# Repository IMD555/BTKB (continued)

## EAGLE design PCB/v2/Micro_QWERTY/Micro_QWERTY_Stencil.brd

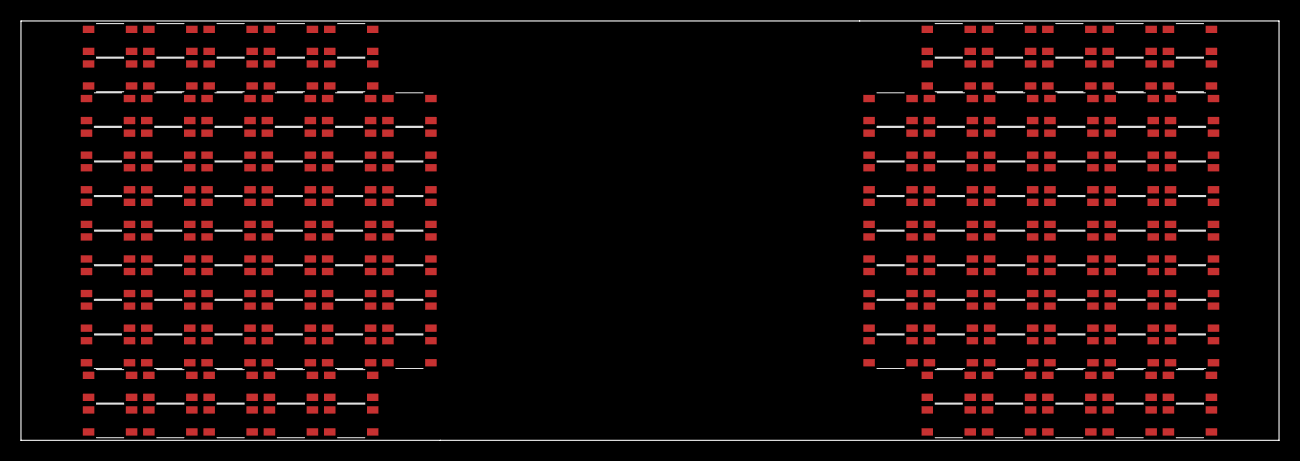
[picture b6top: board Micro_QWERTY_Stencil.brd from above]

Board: 2 copper layers, 120.0 x 40.0 mm, 136 parts (0 on the bottom side), 40 nets, no tracks yet.

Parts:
SW1, SW112: SKRP(ALPS); TVAU10-025
SW2, SW3, SW4, SW5, SW6, SW7, SW8, SW9, SW10, SW11, SW12, SW13, SW14, SW15, SW16, SW17, SW18, SW19, SW20, SW21, SW22, SW23, SW24, SW25, SW26, SW27, SW28, SW29, SW30, SW31, SW32, SW33, SW34, SW35, SW36, SW37, SW38, SW39, SW40, SW41, SW42, SW43, SW44, SW45, SW46, SW47, SW48, SW49, SW50, SW51, SW52, SW53, SW54, SW55, SW56, SW57, SW58, SW59, SW60, SW61, SW62, SW63, SW64, SW65, SW66, SW67, SW68, SW101, SW102, SW103, SW104, SW105, SW106, SW107, SW108, SW109, SW110, SW111, SW113, SW114, SW115, SW116, SW117, SW118, SW119, SW120, SW121, SW122, SW123, SW124, SW125, SW126, SW127, SW128, SW129, SW130, SW131, SW132, SW133, SW134, SW135, SW136, SW137, SW138, SW139, SW140, SW141, SW142, SW143, SW144, SW145, SW146, SW147, SW148, SW149, SW150, SW151, SW152, SW153, SW154, SW155, SW156, SW157, SW158, SW159, SW160, SW163, SW164, SW165, SW166, SW167, SW168, SW169, SW170: SW_4PTVAU10-025; TVAU10-025

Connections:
C0: SW112.P$2, SW124.P$1
C1: SW111.P$2, SW123.P$1
C2: SW122.P$2, SW134.P$1
C3: SW121.P$2, SW133.P$1
C4: SW120.P$2, SW132.P$1
C5: SW119.P$2, SW131.P$1
C6: SW118.P$4, SW130.P$3
C7: SW117.P$4, SW129.P$3
C8: SW116.P$4, SW128.P$3
C9: SW115.P$4, SW127.P$3
C10: SW102.P$4, SW114.P$3
C11: SW101.P$4, SW113.P$3
C12: SW1.P$2, SW2.P$1
C13: SW6.P$2, SW7.P$1
C14: SW12.P$2, SW13.P$1
C15: SW18.P$2, SW19.P$1
C16: SW24.P$2, SW25.P$1
C17: SW30.P$2, SW31.P$1
C18: SW36.P$4, SW37.P$3
C19: SW42.P$4, SW43.P$3
C20: SW48.P$4, SW49.P$3
C21: SW54.P$4, SW55.P$3
C22: SW59.P$4, SW60.P$3
C23: SW64.P$4, SW65.P$3
unnamed: SW123.P$2, SW135.P$1
unnamed: SW114.P$4, SW126.P$3
unnamed: SW7.P$2, SW8.P$1
unnamed: SW60.P$4, SW61.P$3
R0: SW101.P$1, SW102.P$1, SW103.P$1, SW104.P$1, SW105.P$1, SW106.P$1, SW107.P$3, SW108.P$3, SW109.P$3, SW110.P$3, SW111.P$3, SW112.P$3
R1: SW113.P$1, SW114.P$1, SW115.P$1, SW116.P$1, SW117.P$1, SW118.P$1, SW119.P$3, SW120.P$3, SW121.P$3, SW122.P$3, SW123.P$3, SW124.P$3
R2: SW125.P$1, SW126.P$1, SW127.P$1, SW128.P$1, SW129.P$1, SW130.P$1, SW131.P$3, SW132.P$3, SW133.P$3, SW134.P$3, SW135.P$3, SW136.P$3
R3: SW137.P$1, SW138.P$1, SW139.P$1, SW140.P$1, SW141.P$1, SW142.P$1, SW143.P$3, SW144.P$3, SW145.P$3, SW146.P$3, SW147.P$3, SW148.P$3
R4: SW149.P$1, SW150.P$1, SW151.P$1, SW152.P$1, SW153.P$1, SW154.P$1, SW155.P$3, SW156.P$3, SW157.P$3, SW158.P$3, SW159.P$3, SW160.P$3
R5: SW163.P$1, SW164.P$1, SW165.P$1, SW166.P$1, SW167.P$3, SW168.P$3, SW169.P$3, SW170.P$3
R6: SW1.P$3, SW6.P$3, SW11.P$3, SW17.P$3, SW23.P$3, SW29.P$3, SW35.P$1, SW41.P$1, SW47.P$1, SW53.P$1, SW59.P$1, SW64.P$1
R7: SW2.P$3, SW7.P$3, SW12.P$3, SW18.P$3, SW24.P$3, SW30.P$3, SW36.P$1, SW42.P$1, SW48.P$1, SW54.P$1, SW60.P$1, SW65.P$1
R8: SW3.P$3, SW8.P$3, SW13.P$3, SW19.P$3, SW25.P$3, SW31.P$3, SW37.P$1, SW43.P$1, SW49.P$1, SW55.P$1, SW61.P$1, SW66.P$1
R9: SW4.P$3, SW9.P$3, SW14.P$3, SW20.P$3, SW26.P$3, SW32.P$3, SW38.P$1, SW44.P$1, SW50.P$1, SW56.P$1, SW62.P$1, SW67.P$1
R10: SW5.P$3, SW10.P$3, SW15.P$3, SW21.P$3, SW27.P$3, SW33.P$3, SW39.P$1, SW45.P$1, SW51.P$1, SW57.P$1, SW63.P$1, SW68.P$1
R11: SW16.P$3, SW22.P$3, SW28.P$3, SW34.P$3, SW40.P$1, SW46.P$1, SW52.P$1, SW58.P$1

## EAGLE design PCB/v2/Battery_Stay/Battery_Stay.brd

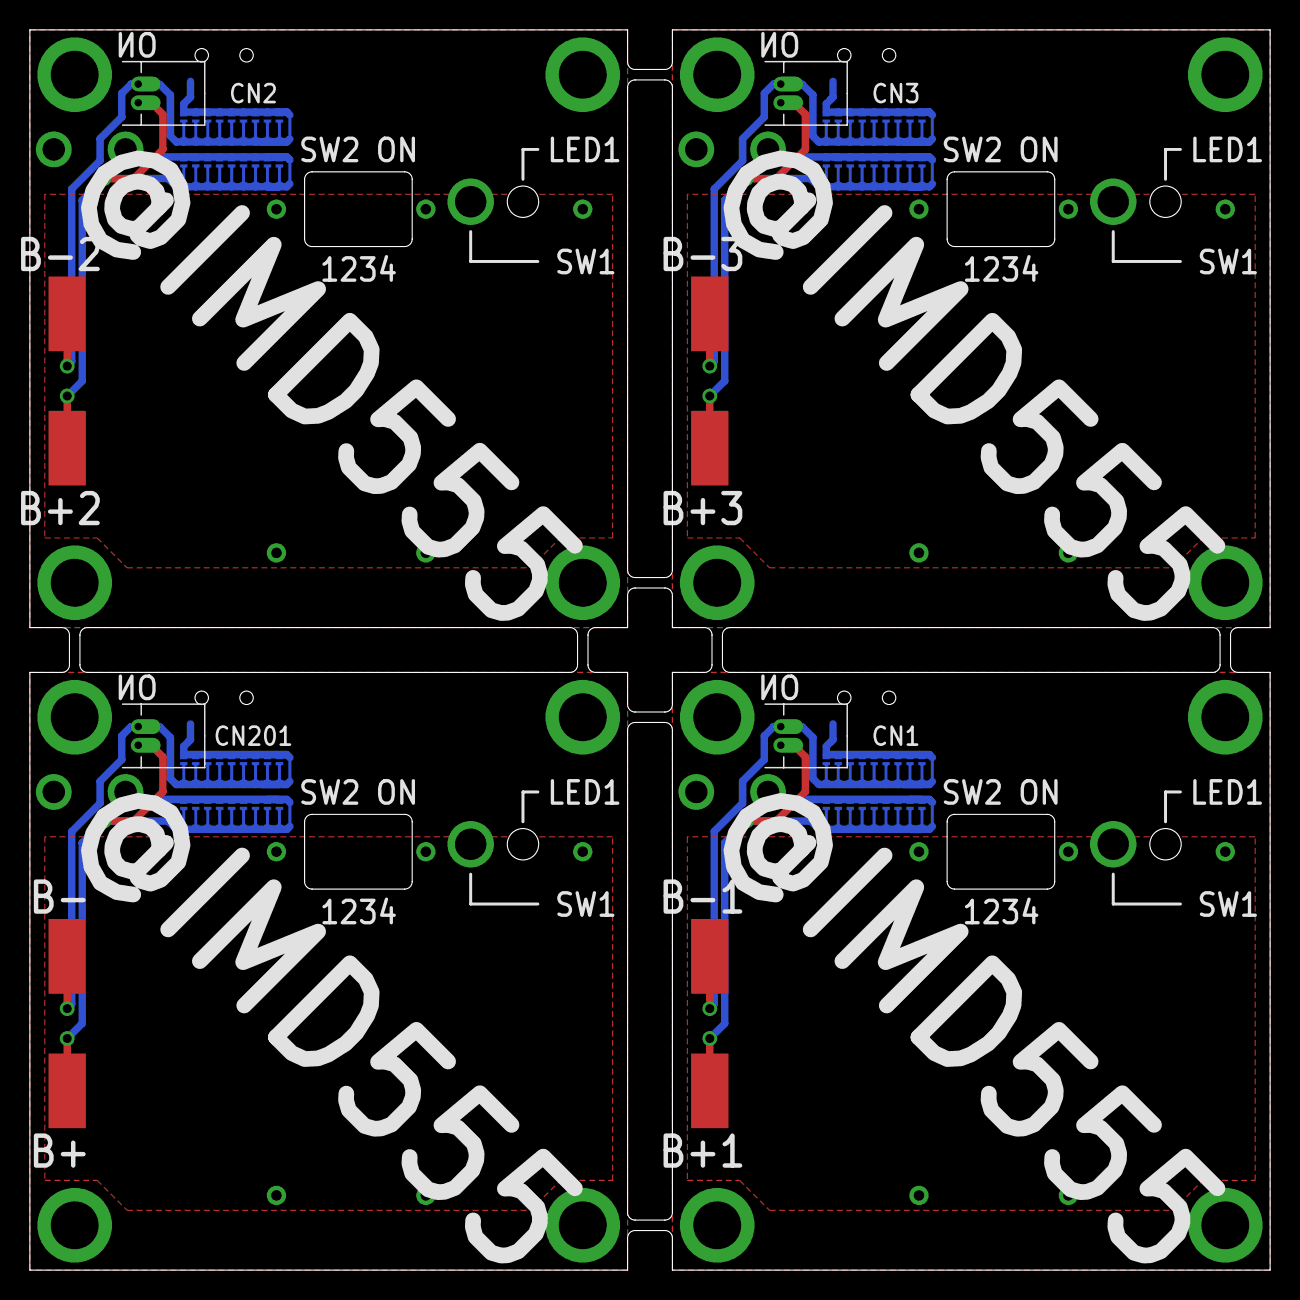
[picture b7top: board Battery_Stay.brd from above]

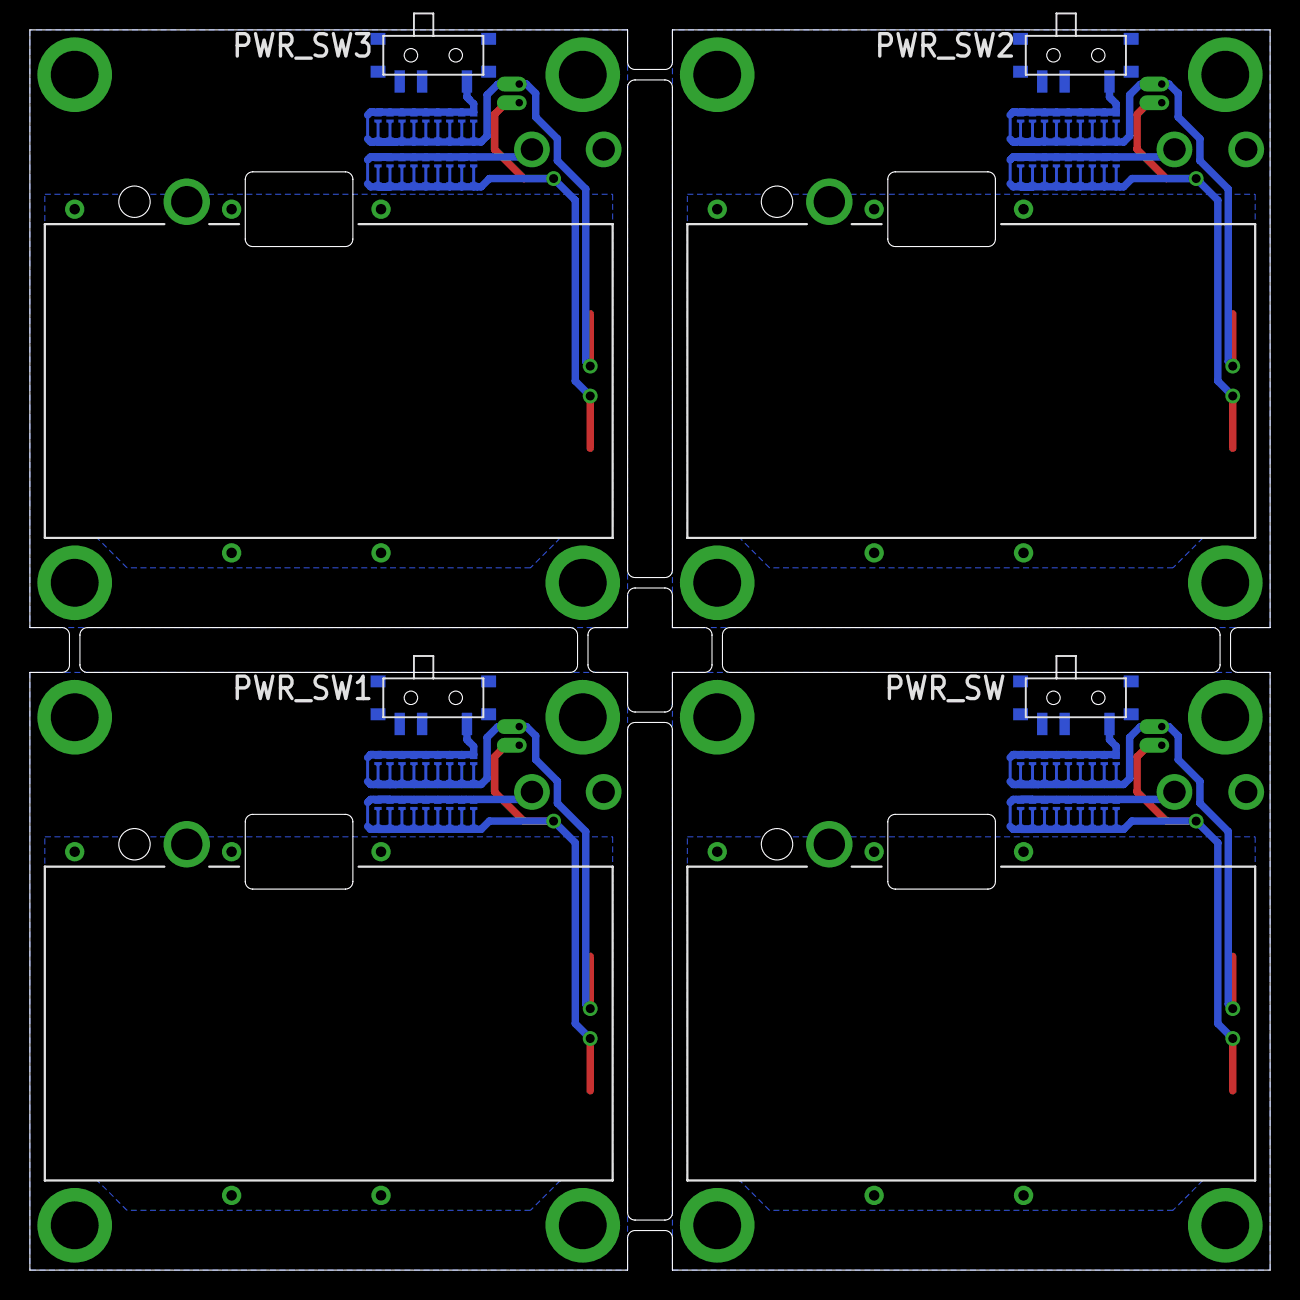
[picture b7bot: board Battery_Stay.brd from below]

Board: 2 copper layers, 83.0 x 83.0 mm, 88 parts (76 on the bottom side), 20 nets.

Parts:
B+, B+1, B+2, B+3: +; SMD2,5-5
B-, B-1, B-2, B-3: -; SMD2,5-5
CN1, CN2, CN3, CN201: 53048-0210
F1, F2, F3, F4, F5, F6, F7, F8, F9, F10, F11, F12, F13, F14, F15, F16, F17, F18, F19, F20, F21, F22, F23, F24, F25, F26, F27, F28, F29, F30, F31, F32, F33, F34, F35, F36, F37, F38, F39, F40, F41, F42, F43, F44, F45, F46, F47, F48, F49, F50, F51, F52, F53, F54, F55, F56, F57, F58, F59, F60, F61, F62, F63, F64, F65, F66, F67, F68, F69, F70, F71, F72: FUSEPAT0.2; FUSE_PAT1
PWR_SW, PWR_SW1, PWR_SW2, PWR_SW3: MA12R

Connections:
GND: PWR_SW.P$2, PWR_SW.P$3, PWR_SW.P$4, PWR_SW.P$5, PWR_SW.P$6, PWR_SW.P$7
GND1: PWR_SW1.P$2, PWR_SW1.P$3, PWR_SW1.P$4, PWR_SW1.P$5, PWR_SW1.P$6, PWR_SW1.P$7
GND2: PWR_SW2.P$2, PWR_SW2.P$3, PWR_SW2.P$4, PWR_SW2.P$5, PWR_SW2.P$6, PWR_SW2.P$7
GND3: PWR_SW3.P$2, PWR_SW3.P$3, PWR_SW3.P$4, PWR_SW3.P$5, PWR_SW3.P$6, PWR_SW3.P$7
unnamed: F1.P$1, F2.P$1, F3.P$1, F4.P$1, F5.P$1, F6.P$1, F13.P$1, F14.P$1, F15.P$1, PWR_SW.P$1
unnamed: B-.1, CN201.2, F1.P$2, F2.P$2, F3.P$2, F4.P$2, F5.P$2, F6.P$2, F13.P$2, F14.P$2, F15.P$2
unnamed: F7.P$1, F8.P$1, F9.P$1, F10.P$1, F11.P$1, F12.P$1, F17.P$1, F18.P$1, F19.P$1
unnamed: B+.1, CN201.1, F7.P$2, F8.P$2, F9.P$2, F10.P$2, F11.P$2, F12.P$2, F17.P$2, F18.P$2, F19.P$2
unnamed: F16.P$1, F23.P$1, F24.P$1, F25.P$1, F26.P$1, F27.P$1, F31.P$1, F32.P$1, F33.P$1, PWR_SW1.P$1
unnamed: B-1.1, CN1.2, F16.P$2, F23.P$2, F24.P$2, F25.P$2, F26.P$2, F27.P$2, F31.P$2, F32.P$2, F33.P$2
unnamed: F20.P$1, F21.P$1, F22.P$1, F28.P$1, F29.P$1, F30.P$1, F34.P$1, F35.P$1, F36.P$1
unnamed: B+1.1, CN1.1, F20.P$2, F21.P$2, F22.P$2, F28.P$2, F29.P$2, F30.P$2, F34.P$2, F35.P$2, F36.P$2
unnamed: F37.P$1, F41.P$1, F42.P$1, F43.P$1, F44.P$1, F45.P$1, F49.P$1, F50.P$1, F51.P$1, PWR_SW2.P$1
unnamed: B-2.1, CN2.2, F37.P$2, F41.P$2, F42.P$2, F43.P$2, F44.P$2, F45.P$2, F49.P$2, F50.P$2, F51.P$2
unnamed: F38.P$1, F39.P$1, F40.P$1, F46.P$1, F47.P$1, F48.P$1, F52.P$1, F53.P$1, F54.P$1
unnamed: B+2.1, CN2.1, F38.P$2, F39.P$2, F40.P$2, F46.P$2, F47.P$2, F48.P$2, F52.P$2, F53.P$2, F54.P$2
unnamed: F55.P$1, F59.P$1, F60.P$1, F61.P$1, F62.P$1, F63.P$1, F67.P$1, F68.P$1, F69.P$1, PWR_SW3.P$1
unnamed: B-3.1, CN3.2, F55.P$2, F59.P$2, F60.P$2, F61.P$2, F62.P$2, F63.P$2, F67.P$2, F68.P$2, F69.P$2
unnamed: F56.P$1, F57.P$1, F58.P$1, F64.P$1, F65.P$1, F66.P$1, F70.P$1, F71.P$1, F72.P$1
unnamed: B+3.1, CN3.1, F56.P$2, F57.P$2, F58.P$2, F64.P$2, F65.P$2, F66.P$2, F70.P$2, F71.P$2, F72.P$2

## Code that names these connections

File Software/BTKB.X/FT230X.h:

#define	USB_CBUS0		RF6
#define	USB_CBUS1		RF7
#define	USB_CBUS3		RF5
#define	USB_PWREN		!USB_CBUS0	//PWREN#
#define	USB_SLEEP		!USB_CBUS1	//SLEEP#
#define	USB_BCD_CHGR	USB_CBUS3	//BCD_Charger
#define USB_UpTo400mA	(USB_PWREN&&!USB_SLEEP)
#define USB_Host		(USB_PWREN&&!USB_SLEEP&&!USB_BCD_CHGR)
#define	USB_SetReady(x)	(LATF0=x)
#define	USB_Ready		RF0

void showText(unsigned char* text);
void showHex2(unsigned char n);
void showHex4(unsigned short n);
void showState(unsigned short v);

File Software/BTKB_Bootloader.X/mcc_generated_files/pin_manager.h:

/**
  @Generated Pin Manager Header File

  @Company:
    Microchip Technology Inc.

  @File Name:
    pin_manager.h

  @Summary:
    This is the Pin Manager file generated using MPLAB(c) Code Configurator

  @Description:
    This header file provides implementations for pin APIs for all pins selected in the GUI.
    Generation Information :
        Product Revision  :  MPLAB(c) Code Configurator - 4.35
        Device            :  PIC18LF67K40
        Version           :  1.01
    The generated drivers are tested against the following:
        Compiler          :  XC8 1.35
        MPLAB             :  MPLAB X 3.40

    Copyright (c) 2013 - 2015 released Microchip Technology Inc.  All rights reserved.

    Microchip licenses to you the right to use, modify, copy and distribute
    Software only when embedded on a Microchip microcontroller or digital signal
    controller that is integrated into your product or third party product
    (pursuant to the sublicense terms in the accompanying license agreement).

    You should refer to the license agreement accompanying this Software for
    additional information regarding your rights and obligations.

    SOFTWARE AND DOCUMENTATION ARE PROVIDED "AS IS" WITHOUT WARRANTY OF ANY KIND,
    EITHER EXPRESS OR IMPLIED, INCLUDING WITHOUT LIMITATION, ANY WARRANTY OF
    MERCHANTABILITY, TITLE, NON-INFRINGEMENT AND FITNESS FOR A PARTICULAR PURPOSE.
    IN NO EVENT SHALL MICROCHIP OR ITS LICENSORS BE LIABLE OR OBLIGATED UNDER
    CONTRACT, NEGLIGENCE, STRICT LIABILITY, CONTRIBUTION, BREACH OF WARRANTY, OR
    OTHER LEGAL EQUITABLE THEORY ANY DIRECT OR INDIRECT DAMAGES OR EXPENSES
    INCLUDING BUT NOT LIMITED TO ANY INCIDENTAL, SPECIAL, INDIRECT, PUNITIVE OR
    CONSEQUENTIAL DAMAGES, LOST PROFITS OR LOST DATA, COST OF PROCUREMENT OF
    SUBSTITUTE GOODS, TECHNOLOGY, SERVICES, OR ANY CLAIMS BY THIRD PARTIES
    (INCLUDING BUT NOT LIMITED TO ANY DEFENSE THEREOF), OR OTHER SIMILAR COSTS.

*/


#ifndef PIN_MANAGER_H
#define PIN_MANAGER_H

#define INPUT   1
#define OUTPUT  0

#define HIGH    1
#define LOW     0

#define ANALOG      1
#define DIGITAL     0

#define PULL_UP_ENABLED      1
#define PULL_UP_DISABLED     0

// get/set RD5 procedures
#define RD5_SetHigh()    do { LATDbits.LATD5 = 1; } while(0)
#define RD5_SetLow()   do { LATDbits.LATD5 = 0; } while(0)
#define RD5_Toggle()   do { LATDbits.LATD5 = ~LATDbits.LATD5; } while(0)
#define RD5_GetValue()         PORTDbits.RD5
#define RD5_SetDigitalInput()   do { TRISDbits.TRISD5 = 1; } while(0)
#define RD5_SetDigitalOutput()  do { TRISDbits.TRISD5 = 0; } while(0)
#define RD5_SetPullup()     do { WPUDbits.WPUD5 = 1; } while(0)
#define RD5_ResetPullup()   do { WPUDbits.WPUD5 = 0; } while(0)
#define RD5_SetAnalogMode() do { ANSELDbits.ANSELD5 = 1; } while(0)
#define RD5_SetDigitalMode()do { ANSELDbits.ANSELD5 = 0; } while(0)

// get/set RD7 procedures
#define RD7_SetHigh()    do { LATDbits.LATD7 = 1; } while(0)
#define RD7_SetLow()   do { LATDbits.LATD7 = 0; } while(0)
#define RD7_Toggle()   do { LATDbits.LATD7 = ~LATDbits.LATD7; } while(0)
#define RD7_GetValue()         PORTDbits.RD7
#define RD7_SetDigitalInput()   do { TRISDbits.TRISD7 = 1; } while(0)
#define RD7_SetDigitalOutput()  do { TRISDbits.TRISD7 = 0; } while(0)
#define RD7_SetPullup()     do { WPUDbits.WPUD7 = 1; } while(0)
#define RD7_ResetPullup()   do { WPUDbits.WPUD7 = 0; } while(0)
#define RD7_SetAnalogMode() do { ANSELDbits.ANSELD7 = 1; } while(0)
#define RD7_SetDigitalMode()do { ANSELDbits.ANSELD7 = 0; } while(0)

// get/set RG2 procedures
#define RG2_SetHigh()    do { LATGbits.LATG2 = 1; } while(0)
#define RG2_SetLow()   do { LATGbits.LATG2 = 0; } while(0)
#define RG2_Toggle()   do { LATGbits.LATG2 = ~LATGbits.LATG2; } while(0)
#define RG2_GetValue()         PORTGbits.RG2
#define RG2_SetDigitalInput()   do { TRISGbits.TRISG2 = 1; } while(0)
#define RG2_SetDigitalOutput()  do { TRISGbits.TRISG2 = 0; } while(0)
#define RG2_SetPullup()     do { WPUGbits.WPUG2 = 1; } while(0)
#define RG2_ResetPullup()   do { WPUGbits.WPUG2 = 0; } while(0)
#define RG2_SetAnalogMode() do { ANSELGbits.ANSELG2 = 1; } while(0)
#define RG2_SetDigitalMode()do { ANSELGbits.ANSELG2 = 0; } while(0)

// get/set RG3 procedures
#define RG3_SetHigh()    do { LATGbits.LATG3 = 1; } while(0)
#define RG3_SetLow()   do { LATGbits.LATG3 = 0; } while(0)
#define RG3_Toggle()   do { LATGbits.LATG3 = ~LATGbits.LATG3; } while(0)
#define RG3_GetValue()         PORTGbits.RG3
#define RG3_SetDigitalInput()   do { TRISGbits.TRISG3 = 1; } while(0)
#define RG3_SetDigitalOutput()  do { TRISGbits.TRISG3 = 0; } while(0)
#define RG3_SetPullup()     do { WPUGbits.WPUG3 = 1; } while(0)
#define RG3_ResetPullup()   do { WPUGbits.WPUG3 = 0; } while(0)
#define RG3_SetAnalogMode() do { ANSELGbits.ANSELG3 = 1; } while(0)
#define RG3_SetDigitalMode()do { ANSELGbits.ANSELG3 = 0; } while(0)

/**
   @Param
    none
   @Returns
    none
   @Description
    GPIO and peripheral I/O initialization
   @Example
    PIN_MANAGER_Initialize();
 */
void PIN_MANAGER_Initialize (void);

/**
 * @Param
    none
 * @Returns
    none
 * @Description
    Interrupt on Change Handling routine
 * @Example
    PIN_MANAGER_IOC();
 */
void PIN_MANAGER_IOC(void);



#endif // PIN_MANAGER_H
/**
 End of File
*/

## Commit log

2021-03-15 rollback later
2021-03-15 rename 2 images
